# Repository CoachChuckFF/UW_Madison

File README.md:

# UW Madison Independent Studies

In my time un University I undertook two independent study projects ( ECE 399 ).

## Mr Choo Choo

Reversed engineered an apple shaped Alphabet toy and added custom hardware to allow for a large button to select the lit up letter so that kiddos with motor function issues can play.

## Modular Power Switcher

This device is meant to be a modular power switcher meant for underprivileged countries to have a cheap and modular power converter for many applications.

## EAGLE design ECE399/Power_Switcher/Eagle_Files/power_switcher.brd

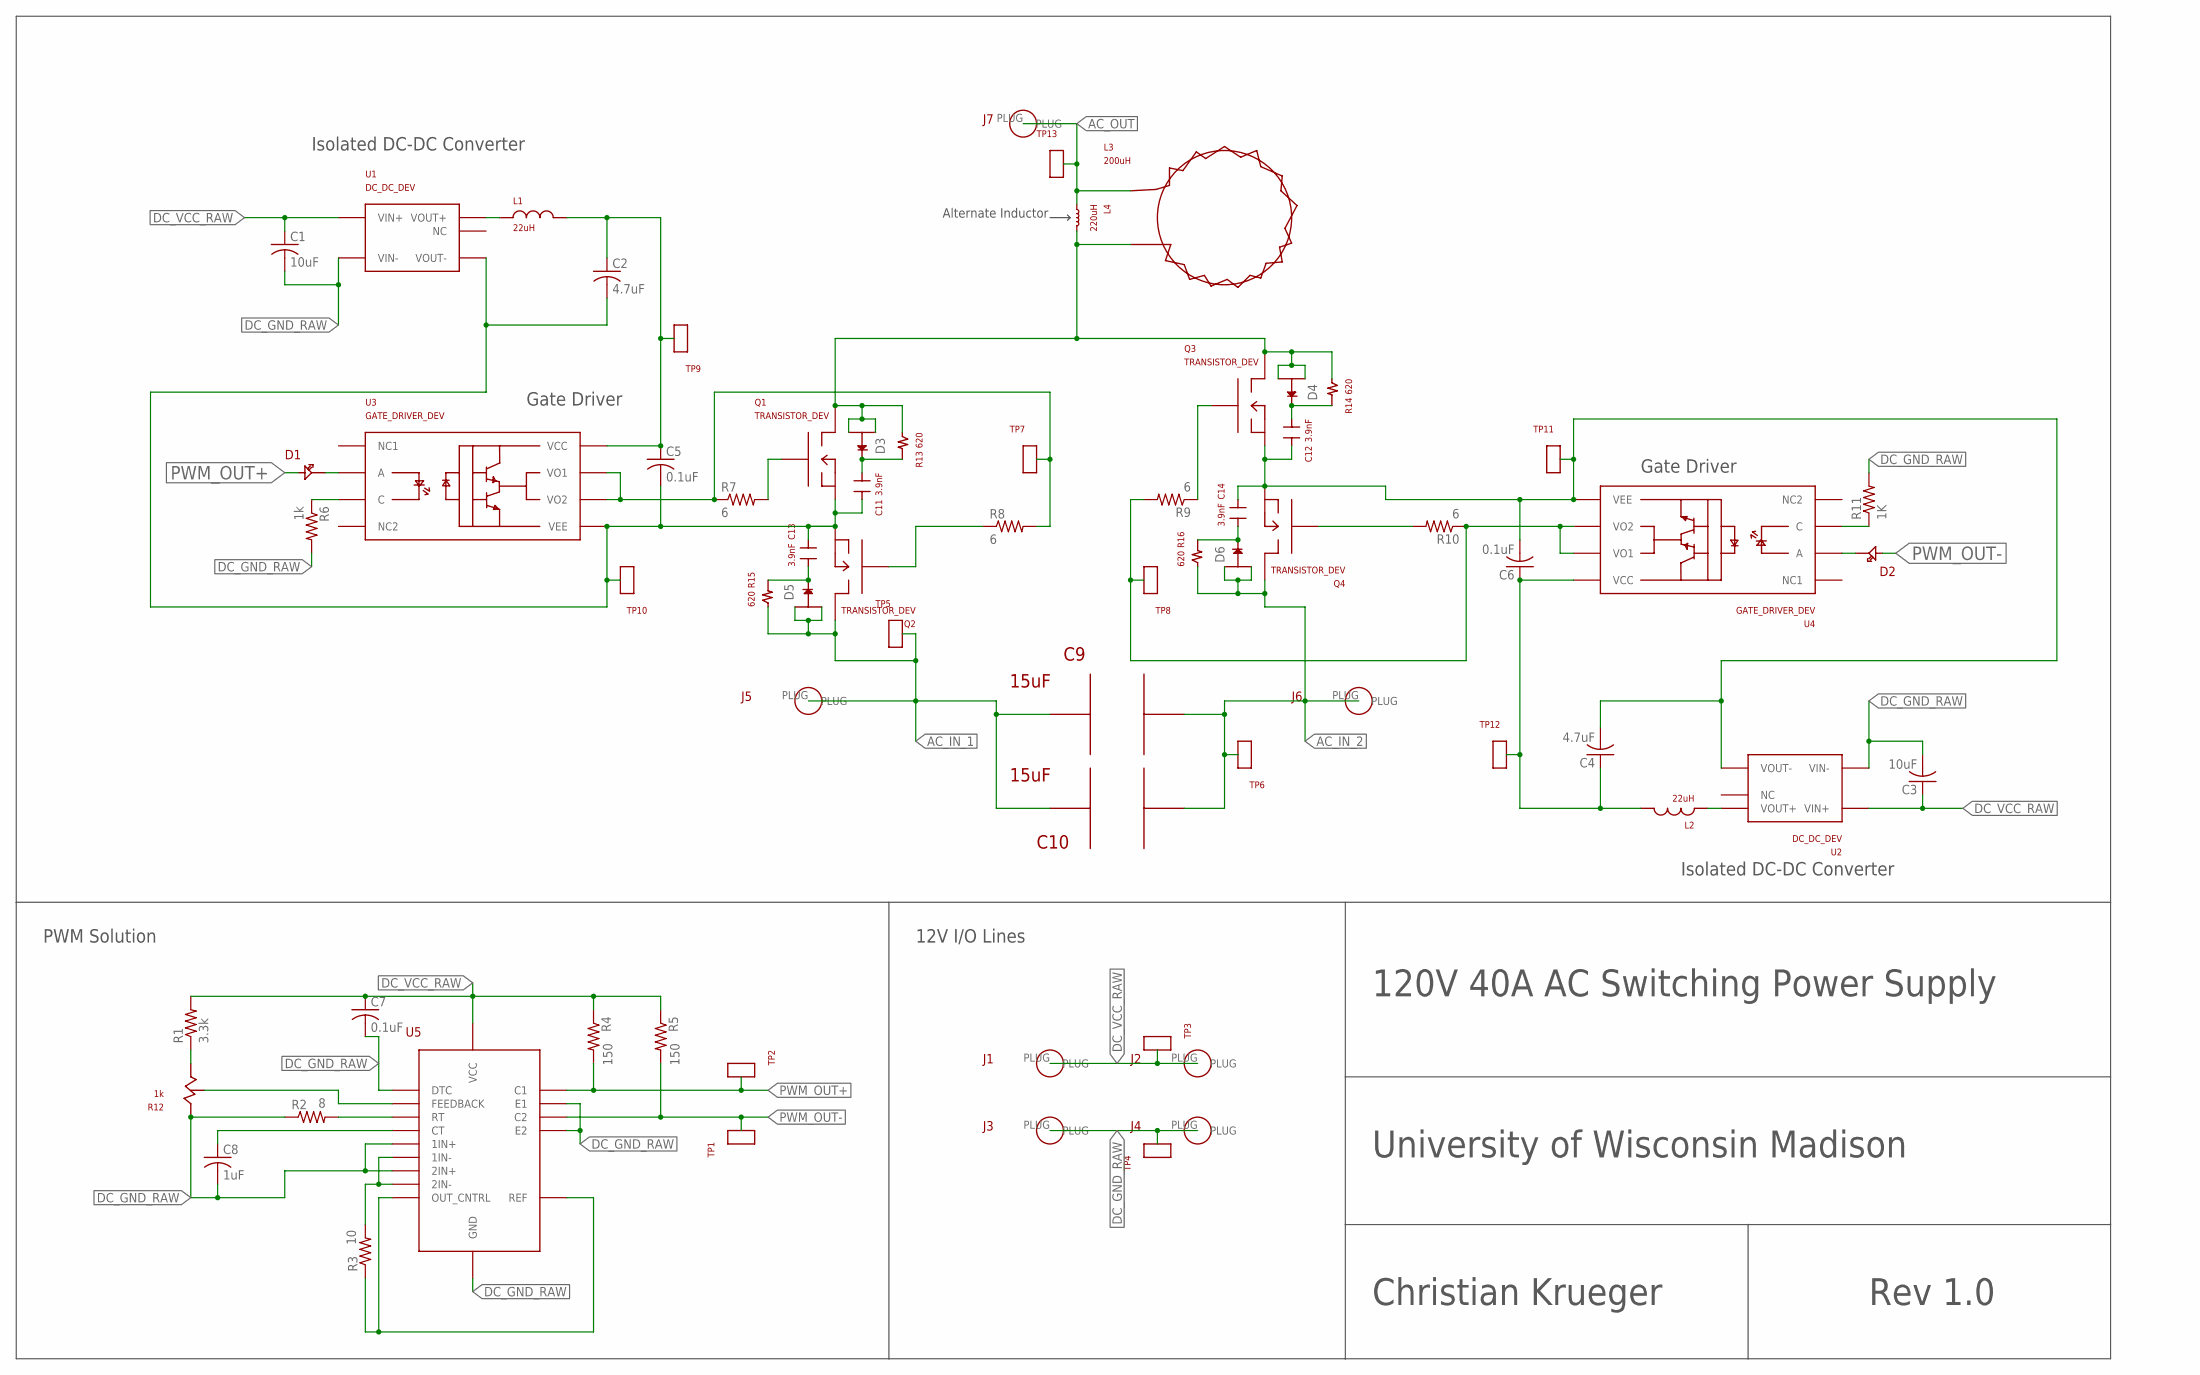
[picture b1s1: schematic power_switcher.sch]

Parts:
C1, C3: 10uF; C0805
C2, C4: 4.7uF; C0805
C5, C6, C7: 0.1uF; C0805
C8: 1uF; C0805
C9, C10: 15uF; BIG_ASS_CAP_PKG
C11, C12, C13, C14: 3.9nF; 0805_GEN_PKG
D1, D2: LED_DEV; 0805_PKG
D3, D4, D5, D6: D2PAK_DIODE_DEV; D2PAK_PKG
J1, J2, J3, J4, J5, J6, J7: BANNANA_DEV; BANNANA_PKG
L1, L2: 22uH; 0805RES_DEV
L3: 200uH; BIG_ASS_INDUCTOR_PKG
L4: 220uH; ALT_IND_PKG
Q1, Q2, Q3, Q4: TRANSISTOR_DEV; TRANSISTOR_PKG
R1: 3.3k; M0805
R2: 8; M0805
R3: 10; M0805
R4, R5: 150; M0805
R6: 1k; M0805
R7, R8, R9, R10: 6; M0805
R11: 1K; M0805
R12: 1k; POT_SLIDER_PKG
R13, R14, R15, R16: 620; 2512_PKG
TP1, TP2, TP3, TP4, TP5, TP6, TP7, TP8, TP9, TP10, TP11, TP12, TP13: TEST_POINT; 0805_GEN_PKG
U1, U2: DC_DC_DEV; DC_DC_PKG
U3, U4: GATE_DRIVER_DEV; GATE_DRIVER_PKG
U5: PWM_DRIVER_DEV; PWM_DRIVER_PKG

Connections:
AC_IN_1: C9.P$1, C10.P$1, D5.IN1, D5.IN2, J5.PLUG, Q2.D (DRAIN), R15.P$1, TP5.P$1
AC_IN_2: C9.P$2, C10.P$2, D6.IN1, D6.IN2, J6.PLUG, Q4.D (DRAIN), R16.P$1, TP6.P$1
AC_OUT: J7.PLUG, L3.P$1, L4.P$1, TP13.P$1
DC_GND_RAW: C1.2, C3.2, C7.2, C8.2, J3.PLUG, J4.PLUG, R2.1, R6.2, R11.2, R12.3 (1), TP4.P$1, U1.-VIN (VIN-), U2.-VIN (VIN-), U5.P$1 (1IN+), U5.P$4 (DTC), U5.P$7 (GND), U5.P$9 (E1), U5.P$10 (E2), U5.P$16 (2IN+)
DC_VCC_RAW: C1.1, C3.1, C7.1, J1.PLUG, J2.PLUG, R1.2, R4.1, R5.1, TP3.P$1, U1.+VIN (VIN+), U2.+VIN (VIN+), U5.P$12 (VCC)
unnamed: C4.1, C6.1, L2.R, TP12.P$1, U4.VCC
unnamed: C2.1, C5.1, L1.R, TP9.P$1, U3.VCC
unnamed: C4.2, C6.2, C12.P$2, C14.P$2, Q3.S (SOURCE), Q4.S (SOURCE), TP11.P$1, U2.-VOUT (VOUT-), U4.VEE
unnamed: R1.1, R12.1 (2)
unnamed: L2.L, U2.+VOUT (VOUT+)
unnamed: L1.L, U1.+VOUT (VOUT+)
unnamed: D1.P$2, U3.A
unnamed: R12.2 (VAR), U5.P$3 (FEEDBACK)
unnamed: R3.1, U5.P$13 (OUT_CNTRL), U5.P$14 (REF)
unnamed: R2.2, U5.P$6 (RT)
unnamed: C8.1, U5.P$5 (CT)
unnamed: R3.2, U5.P$2 (1IN-), U5.P$15 (2IN-)
unnamed: C2.2, C5.2, C11.P$2, C13.P$2, Q1.S (SOURCE), Q2.S (SOURCE), TP10.P$1, U1.-VOUT (VOUT-), U3.VEE
unnamed: R7.1, R8.2, TP7.P$1, U3.VO1, U3.VO2
unnamed: R11.1, U4.C
unnamed: R6.1, U3.C
unnamed: Q1.G (GATE), R7.2
unnamed: Q2.G (GATE), R8.1
unnamed: D2.P$2, U4.A
unnamed: R9.2, R10.1, TP8.P$1, U4.VO1, U4.VO2
unnamed: Q4.G (GATE), R10.2
unnamed: Q3.G (GATE), R9.1
unnamed: C11.P$1, D3.OUT, R13.P$2
unnamed: C12.P$1, D4.OUT, R14.P$2
unnamed: C13.P$1, D5.OUT, R15.P$2
unnamed: C14.P$1, D6.OUT, R16.P$2
PRE_AC_OUT: D3.IN1, D3.IN2, D4.IN1, D4.IN2, L3.P$2, L4.P$2, Q1.D (DRAIN), Q3.D (DRAIN), R13.P$1, R14.P$1
PWM_OUT+: D1.P$1, R4.2, TP2.P$1, U5.P$8 (C1)
PWM_OUT-: D2.P$1, R5.2, TP1.P$1, U5.P$11 (C2)

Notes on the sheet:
120V 40A AC Switching Power Supply
University of Wisconsin Madison
Rev 1.0
Christian Krueger
Gate Driver
Isolated DC-DC Converter
PWM Solution
12V I/O Lines
Alternate Inductor

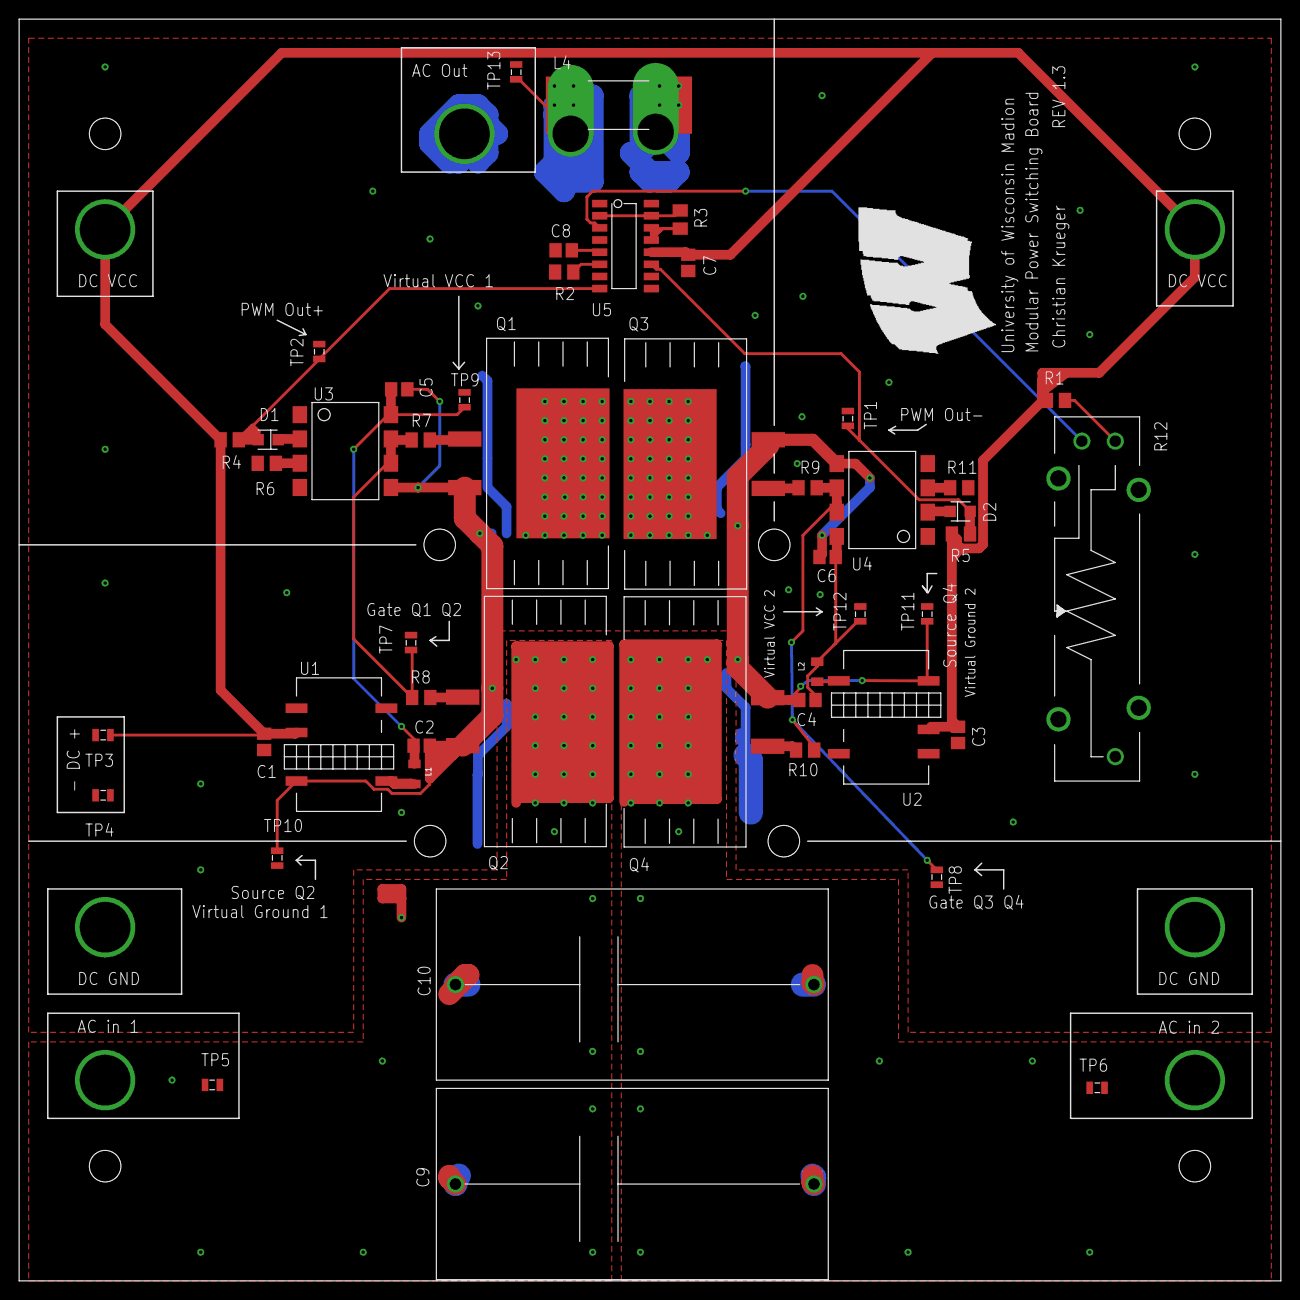
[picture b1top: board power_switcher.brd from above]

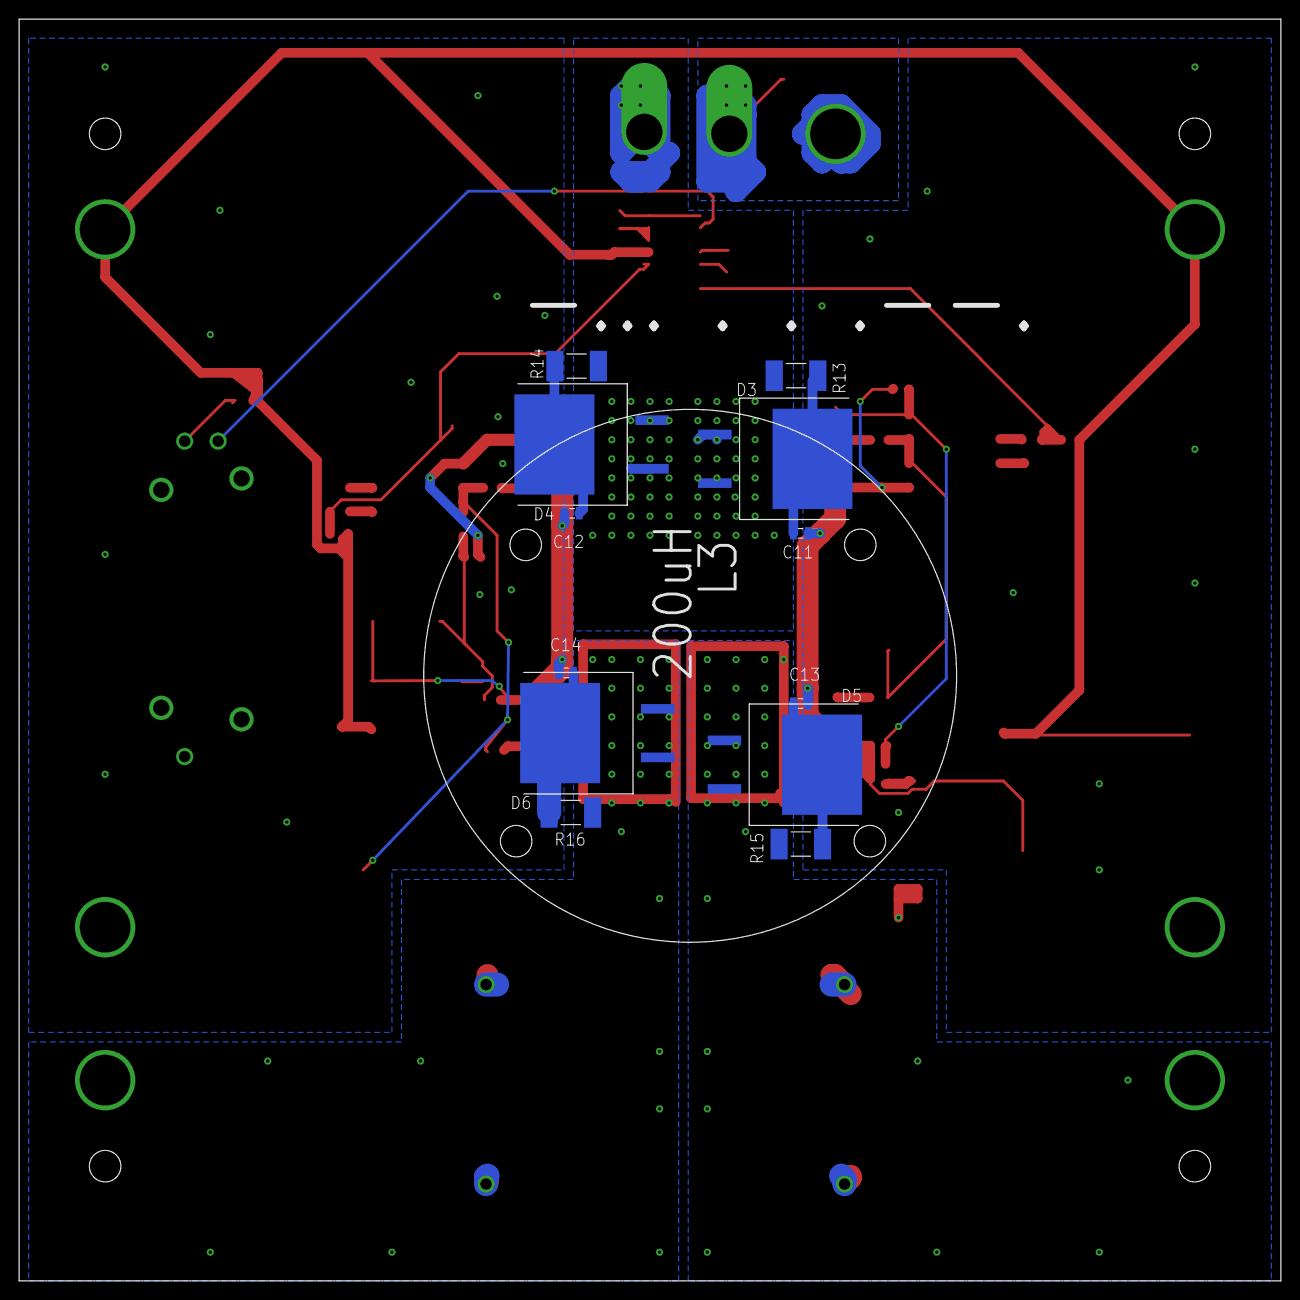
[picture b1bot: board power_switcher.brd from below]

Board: 2 copper layers, 132.0 x 132.0 mm, 69 parts (13 on the bottom side), 34 nets.

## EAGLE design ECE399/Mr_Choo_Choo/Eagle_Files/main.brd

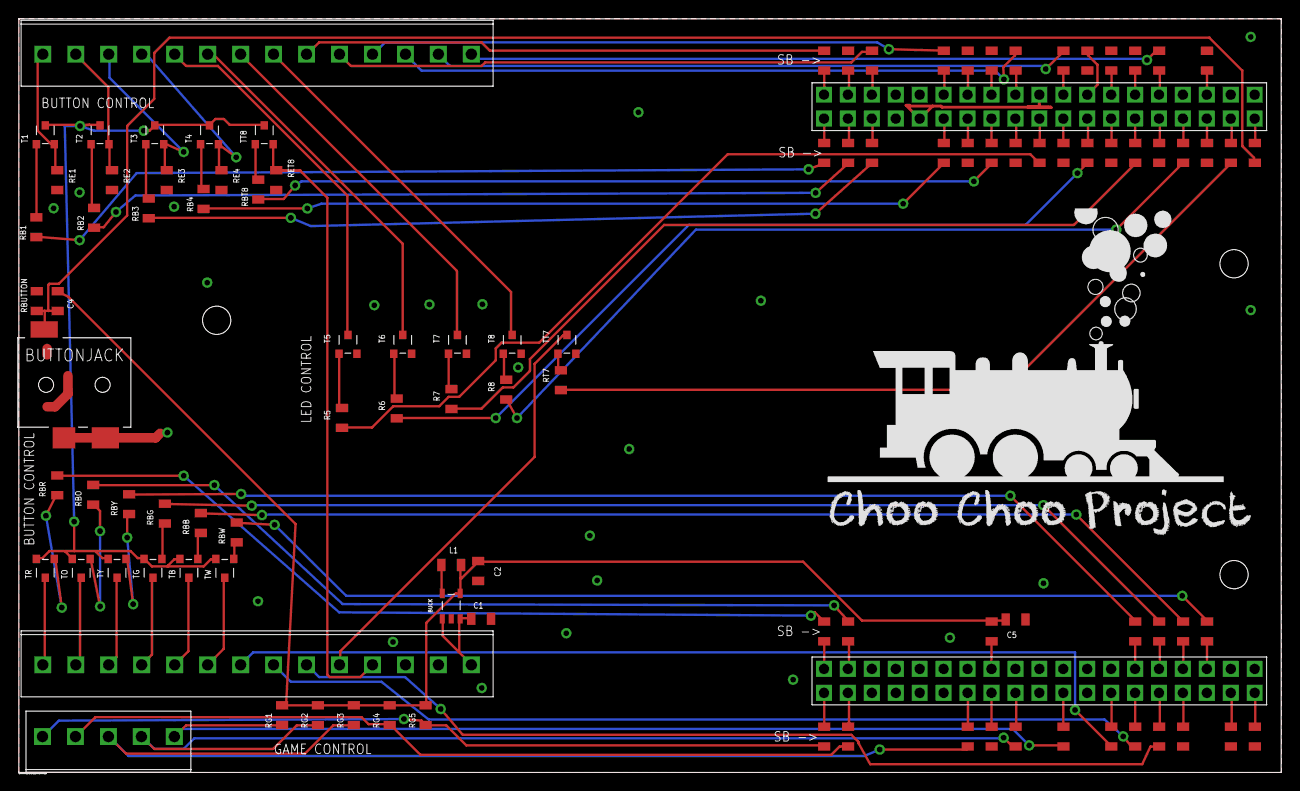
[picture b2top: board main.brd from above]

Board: 2 copper layers, 134.0 x 80.0 mm, 103 parts (0 on the bottom side), 117 nets.

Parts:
BUCK: BUCK_DEV
BUTTONJACK: 3.5MM_MONO_DEV
C1: 4.7uF; 0805RES_DEV
C2: 10uF; 0805RES_DEV
C4, C5: 100nF; 0805RES_DEV
L1: 2.2uH; 0805RES_DEV
NUCLEO-L476RG: NUCLEO_SMALL_DEV
R5, R6, R7, R8: 10k; 0805RES_DEV
RB1, RB2, RB3, RB4: 10k; 0805RES_DEV
RBB: 10k; 0805RES_DEV
RBG: 19k; 0805RES_DEV
RBO: 10k; 0805RES_DEV
RBR: 10k; 0805RES_DEV
RBT8: 10k; 0805RES_DEV
RBUTTON: 10k; 0805RES_DEV
RBW: 10k; 0805RES_DEV
RBY: 10k; 0805RES_DEV
RE1, RE2, RE3, RE4: 4.7k; 0805RES_DEV
RET8: 4.7k; 0805RES_DEV
RG1, RG2, RG3, RG4, RG5: 10k; 0805RES_DEV
RT7: 10k; 0805RES_DEV
SB1, SB2, SB3, SB4, SB5, SB6, SB7, SB8, SB9, SB10, SB11, SB12, SB13, SB14, SB15, SB16, SB17, SB18, SB19, SB20, SB21, SB22, SB23, SB24, SB25, SB26, SB27, SB28, SB29, SB30, SB31, SB32, SB33, SB34, SB35, SB36, SB37, SB38, SB39, SB40, SB41, SB42, SB43, SB44, SB45, SB46, SB47, SB48: 0; 0805RES_DEV
SBPWR: 0; 0805RES_DEV
T1, T2, T3, T4, T5, T6, T7, T8: MMBT2222L_DEV; MMBT2222A_DEV
TB: MMBT2222L_DEV; MMBT2222A_DEV
TG: MMBT2222L_DEV; MMBT2222A_DEV
TO: MMBT2222L_DEV; MMBT2222A_DEV
TR: MMBT2222L_DEV; MMBT2222A_DEV
TT7, TT8: MMBT2222L_DEV; MMBT2222A_DEV
TW: MMBT2222L_DEV; MMBT2222A_DEV
TY: MMBT2222L_DEV; MMBT2222A_DEV
U$2: 5WIRE_TERM_DEV; 5WIRE_DEV
U$3, U$4: 14WIRE_TERM_DEV

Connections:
+3.3V: BUCK.FB, C2.R, C5.R, L1.R, RBUTTON.R, RG1.L, RG2.L, RG3.L, RG4.L, RG5.L, SBPWR.R
B2R1: RB1.L, T1.B
B2R2: RB2.L, T2.B
B2R3: RB3.L, T3.B
B2R5: R5.R, T5.B
B2R6: R6.R, T6.B
B2R7: R7.R, T7.B
B2R8: R8.R, T8.B
B2RT7: RT7.R, TT7.B
B2RT8: RBT8.L, TT8.B
BTR3: RB4.L, T4.B
C2N: T1.C, T2.C, T3.C, T4.C, TB.E, TG.E, TO.E, TR.E, TT8.C, TW.E, TY.E
GND: BUCK.GND, BUTTONJACK.P2, BUTTONJACK.P3, C1.L, C2.L, C4.L, C5.L, NUCLEO-L476RG.P$10, NUCLEO-L476RG.P$23, NUCLEO-L476RG.P$29, NUCLEO-L476RG.P$30, NUCLEO-L476RG.P$43, NUCLEO-L476RG.P$67, RE1.R, RE2.R, RE3.R, RE4.R, RET8.R, T5.E, T6.E, T7.E, T8.E, TT7.E, U$4.P$13
GPIO1: RB1.R, SB19.L
GPIO2: RB2.R, SB20.L
GPIO3: RB3.R, SB21.L
GPIO4: RB4.R, SB22.L
GPIO5: R5.L, SB26.L
GPIO6: R6.L, SB28.L
GPIO7: R7.L, SB30.L
GPIO8: R8.L, SB32.L
GPIO9: SB36.R, U$3.P$9
GPIO10: SB38.R, U$3.P$10
GPIO11: SB39.R, U$3.P$11
GPIO12: SB42.R, U$3.P$12
GPIO13: SB43.R, U$3.P$13
GPIO14: SB47.R, U$3.P$14
GPIOB: RBB.R, SB17.R
GPIOBUTTON: BUTTONJACK.P1, C4.R, RBUTTON.L, SB35.L
GPIOG: RBG.R, SB16.R
GPIOG1: RG1.R, SB6.L, U$2.P$1
GPIOG2: RG2.R, SB5.L, U$2.P$2
GPIOG3: RG3.R, SB3.L, U$2.P$3
GPIOG4: RG4.R, SB2.L, U$2.P$4
GPIOG5: RG5.R, SB1.L, U$2.P$5
GPIOO: RBO.R, SB14.R
GPIOR: RBR.R, SB13.R
GPIOT1: SB7.L, U$4.P$7
GPIOT2: SB8.L, U$4.P$8
GPIOT3: SB9.L, U$4.P$9
GPIOT7: RT7.L, SB34.L
GPIOT8: RBT8.R, SB24.L
GPIOW: RBW.R, SB18.R
GPIOY: RBY.R, SB15.R
unnamed: RBR.L, TR.B
unnamed: NUCLEO-L476RG.P$1, SB1.R
unnamed: RBO.L, TO.B
unnamed: NUCLEO-L476RG.P$2, SB2.R
unnamed: RBY.L, TY.B
unnamed: RBG.L, TG.B
unnamed: RBB.L, TB.B
unnamed: RBW.L, TW.B
unnamed: NUCLEO-L476RG.P$7, SB3.R
unnamed: NUCLEO-L476RG.P$8, SB4.R
unnamed: NUCLEO-L476RG.P$9, SB5.R
unnamed: NUCLEO-L476RG.P$13, SB7.R
unnamed: NUCLEO-L476RG.P$14, SB8.R
unnamed: NUCLEO-L476RG.P$15, SB9.R
unnamed: NUCLEO-L476RG.P$16, SB10.R
unnamed: NUCLEO-L476RG.P$18, SB11.R
unnamed: NUCLEO-L476RG.P$19, SB12.R
unnamed: NUCLEO-L476RG.P$36, SB18.L
unnamed: NUCLEO-L476RG.P$35, SB17.L
unnamed: NUCLEO-L476RG.P$34, SB16.L
unnamed: NUCLEO-L476RG.P$33, SB15.L
unnamed: NUCLEO-L476RG.P$21, SB14.L
unnamed: NUCLEO-L476RG.P$20, SB13.L
unnamed: NUCLEO-L476RG.P$39, SB19.R
unnamed: NUCLEO-L476RG.P$40, SB20.R
unnamed: NUCLEO-L476RG.P$41, SB21.R
unnamed: NUCLEO-L476RG.P$44, SB22.R
unnamed: NUCLEO-L476RG.P$45, SB23.R
unnamed: NUCLEO-L476RG.P$46, SB24.R
unnamed: NUCLEO-L476RG.P$47, SB25.R
unnamed: NUCLEO-L476RG.P$48, SB26.R
unnamed: NUCLEO-L476RG.P$49, SB27.R
unnamed: NUCLEO-L476RG.P$11, SB6.R
unnamed: NUCLEO-L476RG.P$50, SB28.R
unnamed: NUCLEO-L476RG.P$51, SB29.R
unnamed: NUCLEO-L476RG.P$52, SB30.R
unnamed: NUCLEO-L476RG.P$53, SB31.R
unnamed: NUCLEO-L476RG.P$54, SB32.R
unnamed: NUCLEO-L476RG.P$55, SB33.R
unnamed: NUCLEO-L476RG.P$56, SB34.R
unnamed: NUCLEO-L476RG.P$57, SB35.R
unnamed: NUCLEO-L476RG.P$58, SB36.L
unnamed: NUCLEO-L476RG.P$59, SB37.L
unnamed: NUCLEO-L476RG.P$60, SB38.L
unnamed: NUCLEO-L476RG.P$68, SB43.L
unnamed: NUCLEO-L476RG.P$69, SB44.L
unnamed: NUCLEO-L476RG.P$63, SB39.L
unnamed: NUCLEO-L476RG.P$64, SB40.L
unnamed: NUCLEO-L476RG.P$65, SB41.L
unnamed: NUCLEO-L476RG.P$66, SB42.L
unnamed: NUCLEO-L476RG.P$70, SB45.L
unnamed: NUCLEO-L476RG.P$71, SB46.L
unnamed: NUCLEO-L476RG.P$72, SB47.L
unnamed: NUCLEO-L476RG.P$74, SB48.L
unnamed: NUCLEO-L476RG.P$27, SBPWR.L
P1: RE1.L, T1.E, U$3.P$1
P2: RE2.L, T2.E, U$3.P$2
P3: RE3.L, T3.E, U$3.P$3
P4: RE4.L, T4.E, U$3.P$4
P5: T5.C, U$3.P$5
P6: T6.C, U$3.P$6
P7: T7.C, U$3.P$7
P8: T8.C, U$3.P$8
PB: TB.C, U$4.P$5
PG: TG.C, U$4.P$4
PO: TO.C, U$4.P$2
PR: TR.C, U$4.P$1
PT7: TT7.C, U$4.P$10
PT8: RET8.L, TT8.E, U$4.P$11
PW: TW.C, U$4.P$6
PY: TY.C, U$4.P$3
SW2L1: BUCK.SW, L1.L
VCC: BUCK.EN, BUCK.VIN, C1.R, U$4.P$14

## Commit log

2017-11-08 first
2017-11-08 diodes moved for Giri
2017-11-15 right diode added
2023-11-10 working
2023-11-10 images added
2023-11-11 pics added
